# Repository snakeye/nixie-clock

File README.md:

# Nixie Clock

An ESP32-C3 powered Nixie clock built around custom KiCad hardware and Arduino firmware.

## Boards

### Main board

### Indicator board

## What this is

This repository contains the hardware and firmware for a four-digit Nixie clock.
It uses Wi-Fi to sync time from NTP, drives the tubes with a multiplexed display stage, and keeps the high-voltage supply disabled until the clock has a valid time.

## Features

- Wi-Fi time sync via NTP
- Automatic high-voltage safety control
- OTA firmware updates
- Manual cathode cleaning from a button long-press
- Automatic daily cathode cleaning at midnight
- KiCad hardware for the main clock board and indicator board

## Key components

- IN-14 Nixie tubes
- 155ИД1 high-voltage digit driver
- ESP32-C3 SuperMini module
- 74HC595 shift register
- TLP627 optocouplers
- Nixie Tube Boost Converter module
- WS2812B RGB status LED
- USB-C power input
- Two push buttons

### High-voltage boost module

I've used this particular module found on AliExpress. It features voltage adjustment. Other modules should also work, but they'll require proper wiring. 

## How it works

The firmware boots in a safe state with the display blanked and the high-voltage rail off.
After Wi-Fi connects and NTP provides a valid time, the clock enables the high-voltage section and starts showing the current time.

When a successful sync happens, the firmware opens a short OTA maintenance window. If an upload starts, the high-voltage rail is disabled while the update is in progress.

Button 1 has a long-press action that starts cathode cleaning manually. The same cleaning routine also runs automatically once per day when the clock reaches midnight.

## Repository layout

- `firmware/` - PlatformIO project for the ESP32-C3
- `hardware/main/` - main KiCad project for the clock board
- `hardware/indicators/` - indicator-board KiCad project
- `docs/` - photos and other documentation assets

## Firmware setup

1. Open `firmware/` in PlatformIO or your preferred VS Code setup.
2. Copy `firmware/src/config.h.example` to `firmware/src/config.h`.
3. Fill in your Wi-Fi SSID and password.
4. Build and upload the `esp32c3` environment.

The firmware is configured for the `esp32-c3-devkitm-1` board.

## Notes

- The clock currently uses a CET/CEST timezone definition in firmware.
- The firmware hostname is `nixie-clock`.
- `firmware/src/config.h` is ignored by Git so local Wi-Fi credentials stay machine-specific.

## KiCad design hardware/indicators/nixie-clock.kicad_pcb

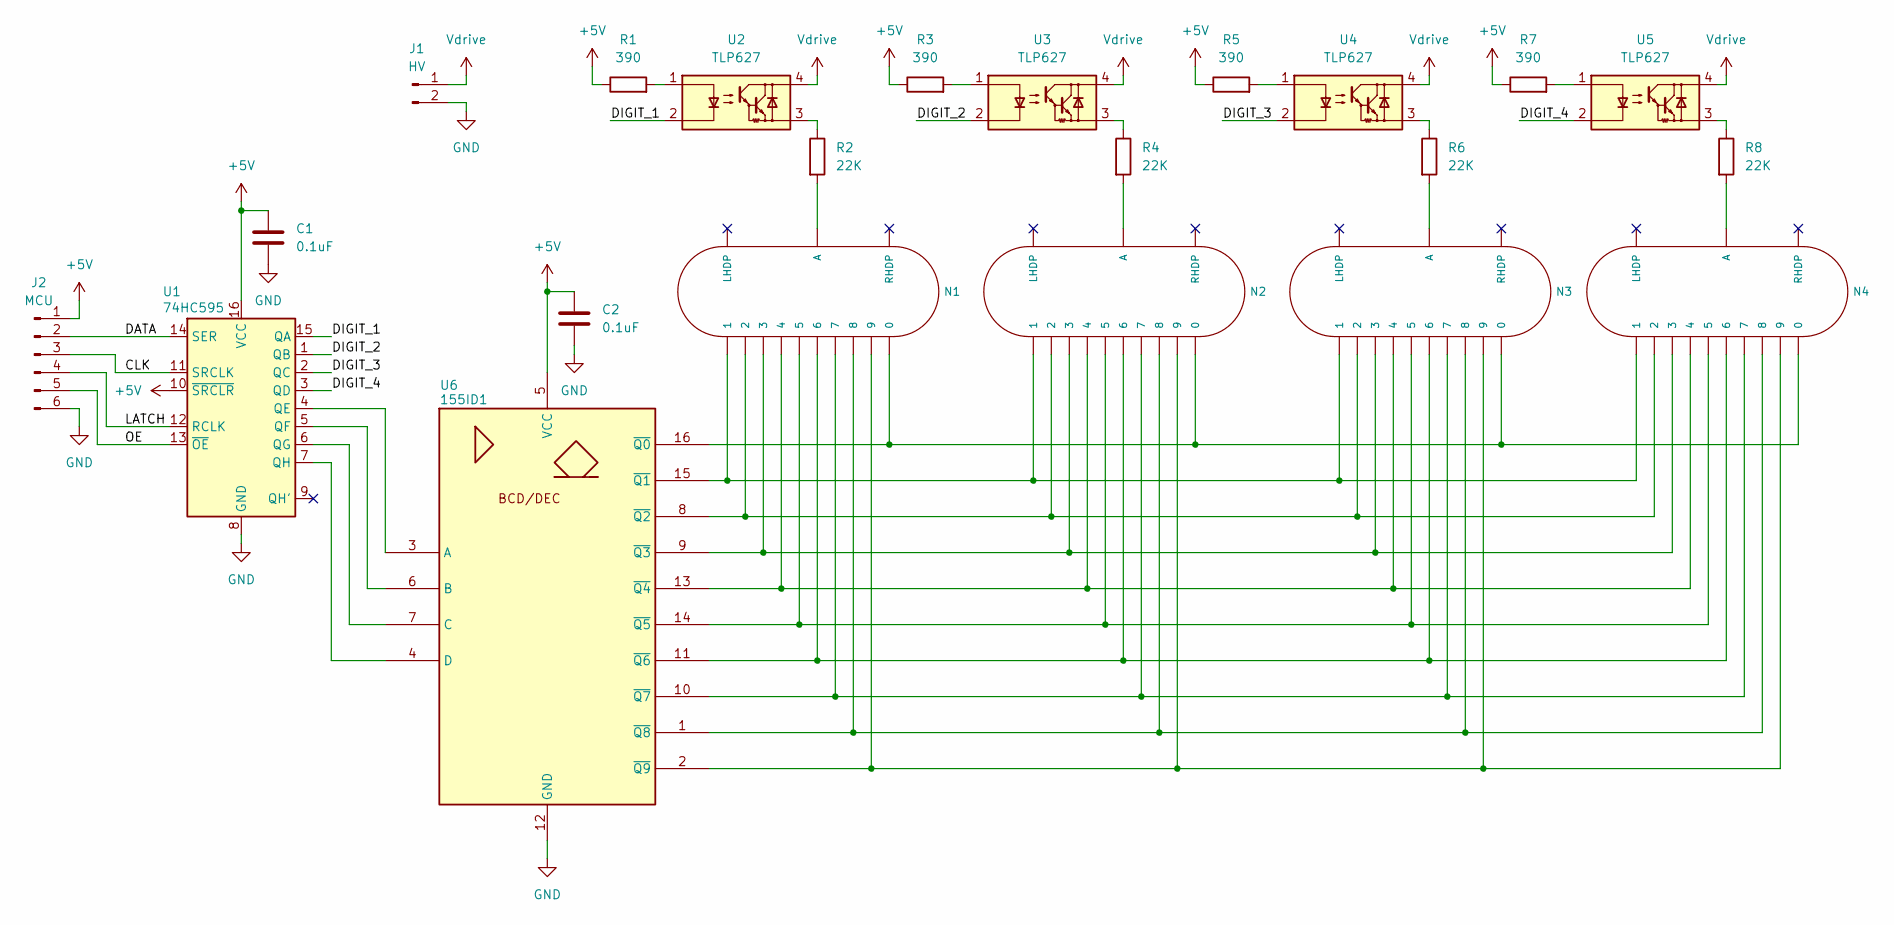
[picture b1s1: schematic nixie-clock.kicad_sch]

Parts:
C1, C2: 0.1uF; C_0805_2012Metric
J1: HV; PinSocket_1x02_P2.54mm_Vertical
J2: MCU; PinSocket_1x06_P2.54mm_Vertical
N1, N2, N3, N4: IN-14; nixies-us-IN-14
R1, R3, R5, R7: 390; R_Axial_DIN0207_L6.3mm_D2.5mm_P7.62mm_Horizontal
R2, R4, R6, R8: 22K; R_Axial_DIN0207_L6.3mm_D2.5mm_P7.62mm_Horizontal
U1: 74HC595; SOP-16_4.4x10.4mm_P1.27mm
U2, U3, U4, U5: TLP627; DIP-4_W7.62mm
U6: 155ID1; DIP-16_W7.62mm

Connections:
+5V: C1.1, C2.1, J2.1, R1.1, R3.1, R5.1, R7.1, U1.10 (~SRCLR), U1.16 (VCC), U6.5 (VCC)
/CLK: J2.3, U1.11 (SRCLK)
/DATA: J2.2, U1.14 (SER)
/DIGIT_1: U1.15 (QA), U2.2
/DIGIT_2: U1.1 (QB), U3.2
/DIGIT_3: U1.2 (QC), U4.2
/DIGIT_4: U1.3 (QD), U5.2
/LATCH: J2.4, U1.12 (RCLK)
/OE: J2.5, U1.13 (~OE)
GND: C1.2, C2.2, J1.2, J2.6, U1.8 (GND), U6.12 (GND)
unnamed: N1.A, R2.2
unnamed: N2.A, R4.2
unnamed: N3.A, R6.2
unnamed: N4.A, R8.2
unnamed: R1.2, U2.1
unnamed: R2.1, U2.3
unnamed: R3.2, U3.1
unnamed: R4.1, U3.3
unnamed: R5.2, U4.1
unnamed: R6.1, U4.3
unnamed: R7.2, U5.1
unnamed: R8.1, U5.3
unnamed: U1.4 (QE), U6.3 (A)
unnamed: U1.5 (QF), U6.6 (B)
unnamed: U1.6 (QG), U6.7 (C)
unnamed: U1.7 (QH), U6.4 (D)
unnamed: N1.0, N2.0, N3.0, N4.0, U6.16 (~Q0)
unnamed: N1.1, N2.1, N3.1, N4.1, U6.15 (~Q1)
unnamed: N1.2, N2.2, N3.2, N4.2, U6.8 (~Q2)
unnamed: N1.3, N2.3, N3.3, N4.3, U6.9 (~Q3)
unnamed: N1.4, N2.4, N3.4, N4.4, U6.13 (~Q4)
unnamed: N1.5, N2.5, N3.5, N4.5, U6.14 (~Q5)
unnamed: N1.6, N2.6, N3.6, N4.6, U6.11 (~Q6)
unnamed: N1.7, N2.7, N3.7, N4.7, U6.10 (~Q7)
unnamed: N1.8, N2.8, N3.8, N4.8, U6.1 (~Q8)
unnamed: N1.9, N2.9, N3.9, N4.9, U6.2 (~Q9)
Vdrive: J1.1, U2.4, U3.4, U4.4, U5.4

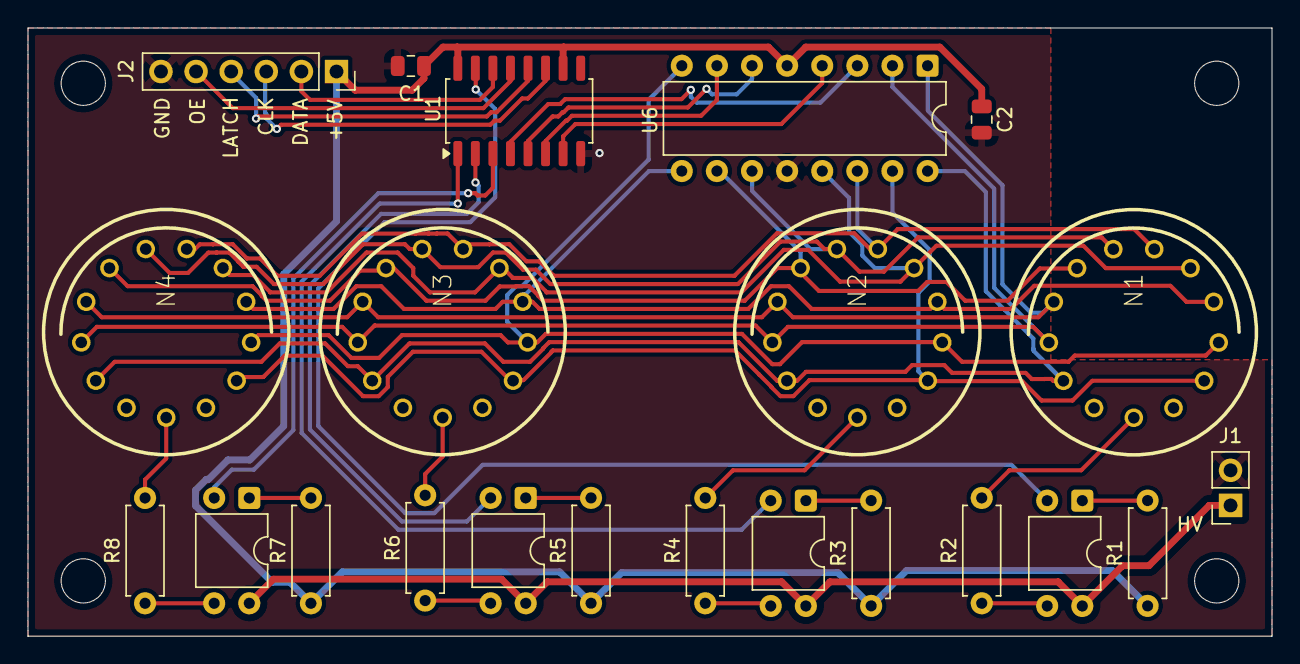
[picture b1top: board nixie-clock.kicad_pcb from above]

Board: 2 copper layers, 90.0 x 44.0 mm, 22 parts (0 on the bottom side), 37 nets.

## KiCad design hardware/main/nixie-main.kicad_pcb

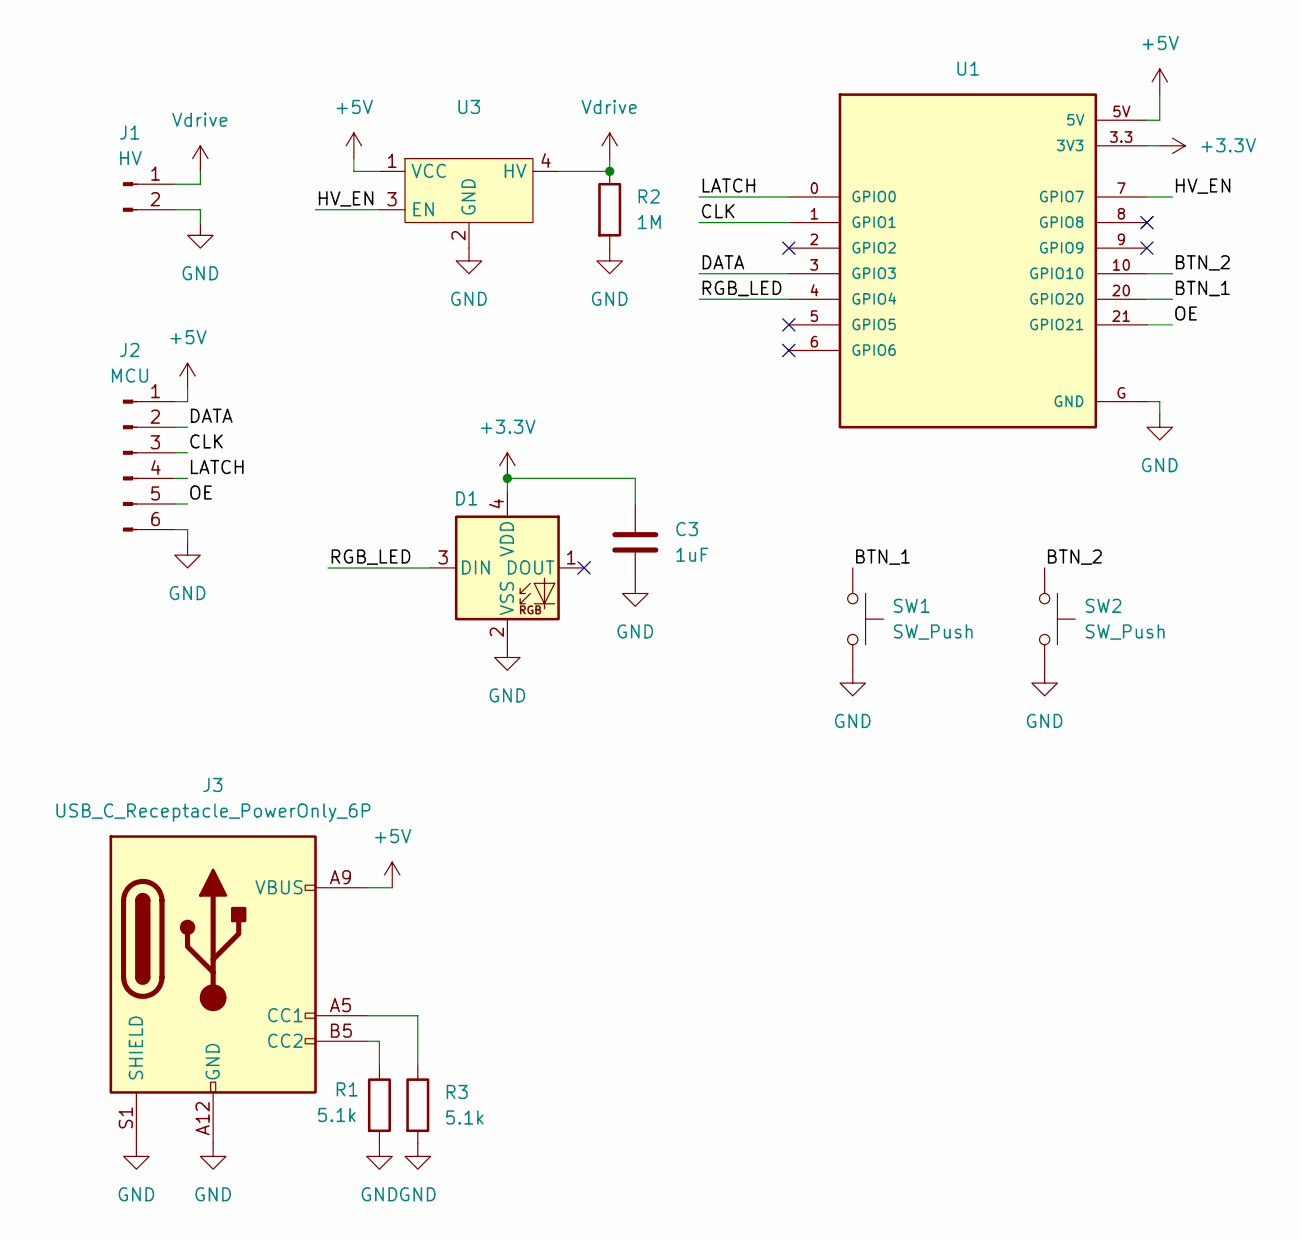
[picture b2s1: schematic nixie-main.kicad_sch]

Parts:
C3: 1uF; C_0805_2012Metric
D1: WS2812B-2020; LED_WS2812B-2020_PLCC4_2.0x2.0mm
J1: HV; PinSocket_1x02_P2.54mm_Vertical
J2: MCU; PinSocket_1x06_P2.54mm_Vertical
J3: USB_C_Receptacle_PowerOnly_6P; USB_C_Receptacle_HRO_TYPE-C-31-M-17
R1, R3: 5.1k; R_0603_1608Metric
R2: 1M; R_Axial_DIN0207_L6.3mm_D2.5mm_P7.62mm_Horizontal
SW1, SW2: SW_Push; BUTTON
U1: ESP32-C3_SUPERMINI; MODULE_ESP32-C3_SUPERMINI_TH
U3: SIP-5

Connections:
+3.3V: C3.1, D1.4 (VDD), U1.3.3 (3V3)
+5V: J2.1, J3.A9 (VBUS), J3.B9 (VBUS), U1.5V, U3.1 (VCC)
/BTN_1: SW1.1, U1.20 (GPIO20)
/BTN_2: SW2.1, U1.10 (GPIO10)
/CLK: J2.3, U1.1 (GPIO1)
/DATA: J2.2, U1.3 (GPIO3)
/HV_EN: U1.7 (GPIO7), U3.3 (EN)
/LATCH: J2.4, U1.0 (GPIO0)
/OE: J2.5, U1.21 (GPIO21)
/RGB_LED: D1.3 (DIN), U1.4 (GPIO4)
GND: C3.2, D1.2 (VSS), J1.2, J2.6, J3.A12 (GND), J3.B12 (GND), J3.S1 (SHIELD), R1.2, R2.2, R3.2, SW1.2, SW2.2, U1.G (GND), U3.2 (GND)
unnamed: J3.A5 (CC1), R3.1
unnamed: J3.B5 (CC2), R1.1
Vdrive: J1.1, R2.1, U3.4 (HV)

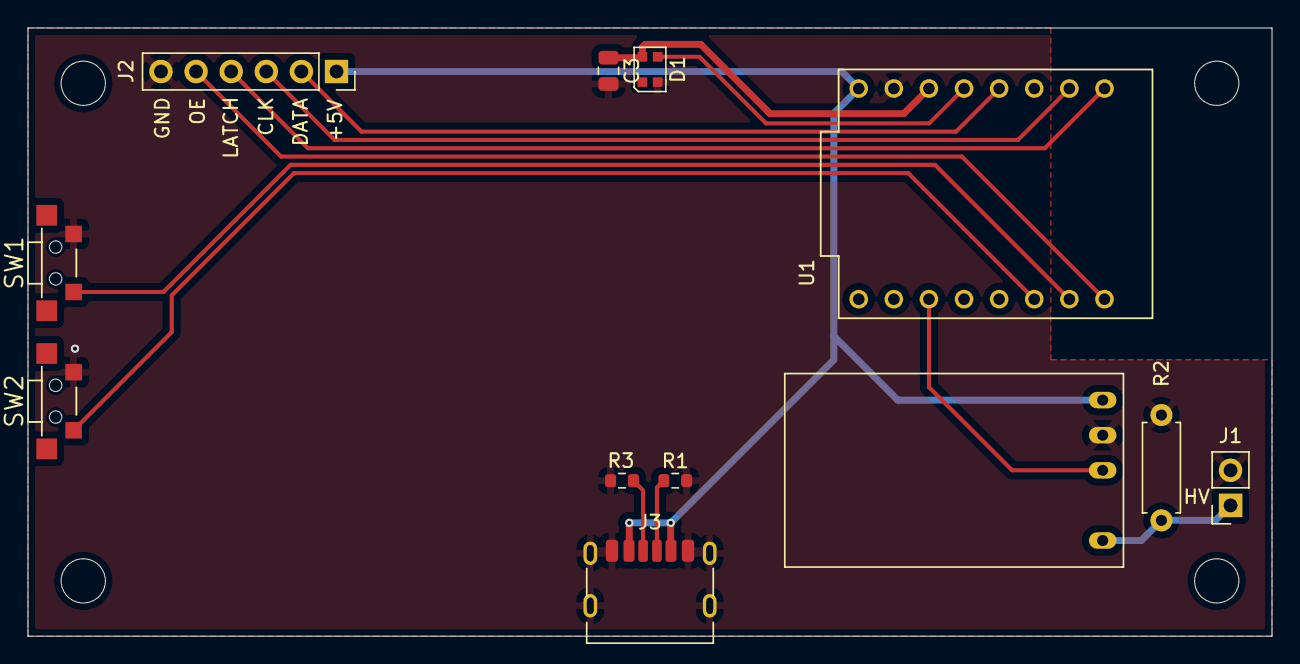
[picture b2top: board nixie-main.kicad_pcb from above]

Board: 2 copper layers, 90.0 x 44.0 mm, 12 parts (0 on the bottom side), 14 nets.

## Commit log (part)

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2020-03-29 Board design
